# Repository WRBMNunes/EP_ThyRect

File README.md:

# EP_ThyRect
Educational plataform of closed-loop controlled thyristor rectifier designed to teach control systems

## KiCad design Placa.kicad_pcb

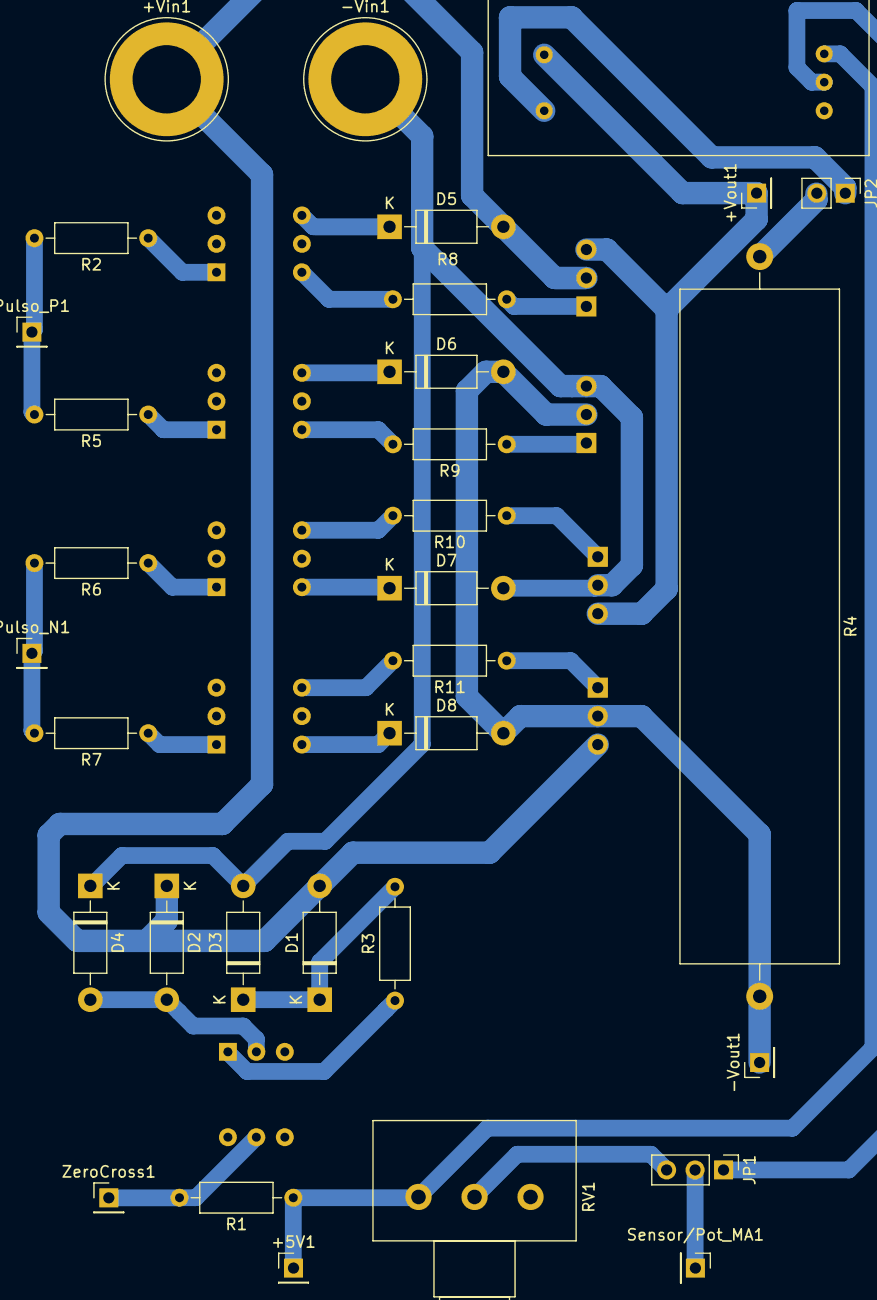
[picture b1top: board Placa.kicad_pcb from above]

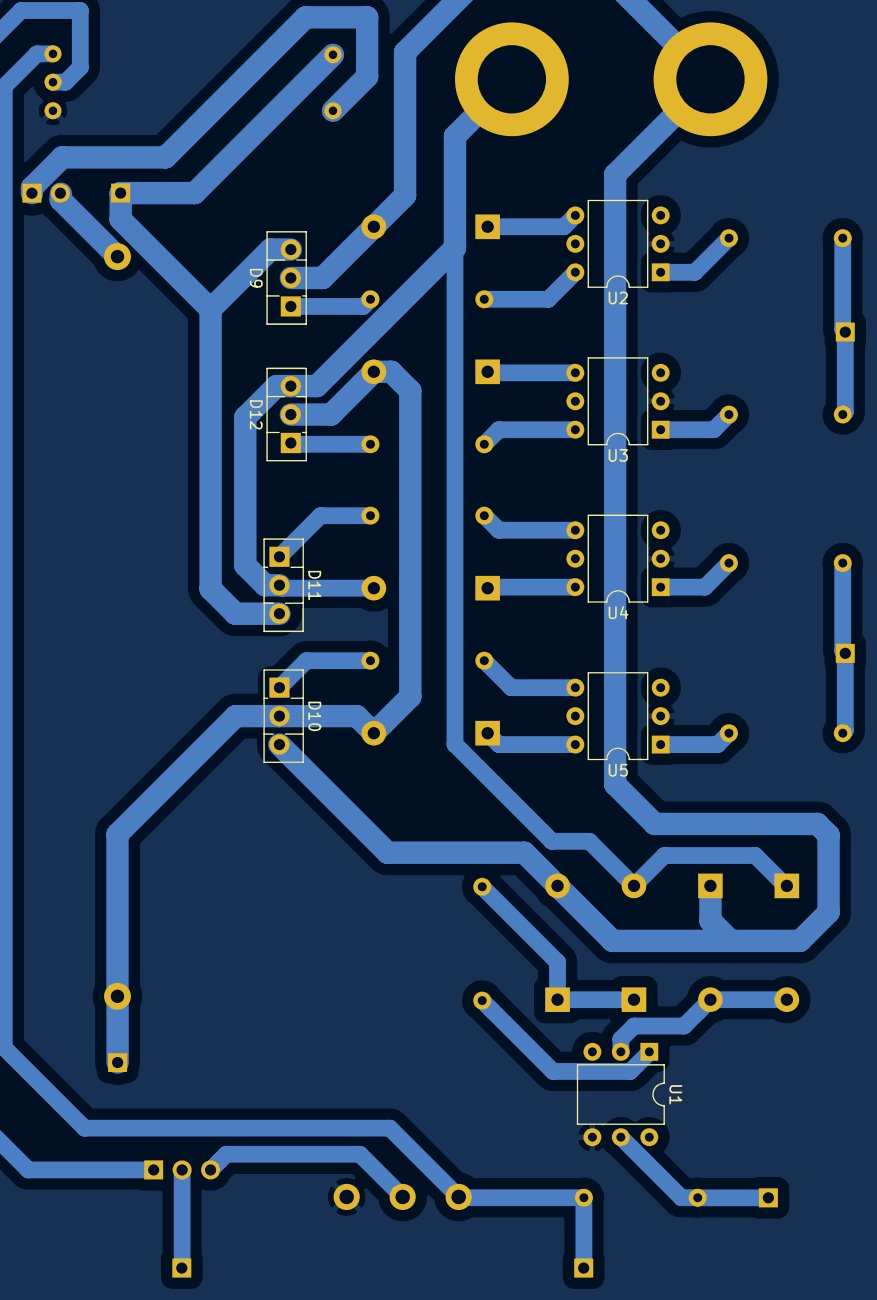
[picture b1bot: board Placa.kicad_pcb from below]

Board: 2 copper layers, 41 parts (9 on the bottom side), 33 nets.

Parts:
+5V1: Conn_01x01_Male; PinHeader_1x01_P2.54mm_Vertical
+Vin1: Conn_01x01_Female; Banana_Jack_1Pin
+Vout1: Conn_01x01_Female; PinHeader_1x01_P2.54mm_Vertical
-Vin1: Conn_01x01_Female; Banana_Jack_1Pin
-Vout1: Conn_01x01_Female; PinHeader_1x01_P2.54mm_Vertical
D1, D2, D3, D4, D5, D6, D7, D8: 1N4007; D_DO-41_SOD81_P10.16mm_Horizontal
D9, D10, D11, D12: Q_SCR_GAK; TO-126-3_Vertical
JP1: Jumper_3_Open; PinHeader_1x03_P2.54mm_Vertical
JP2: Jumper; PinHeader_1x02_P2.54mm_Vertical
Pulso_N1: Conn_01x01_Female; PinHeader_1x01_P2.54mm_Vertical
Pulso_P1: Conn_01x01_Female; PinHeader_1x01_P2.54mm_Vertical
R1: 10k; R_Axial_DIN0207_L6.3mm_D2.5mm_P10.16mm_Horizontal
R2, R5, R6, R7, R8, R9, R10, R11: 120; R_Axial_DIN0207_L6.3mm_D2.5mm_P10.16mm_Horizontal
R3: 470; R_Axial_DIN0207_L6.3mm_D2.5mm_P10.16mm_Horizontal
R4: 15; R_Axial_Power_L60.0mm_W14.0mm_P66.04mm
RV1: R_POT; Potentiometer_Alps_RK163_Single_Horizontal
Sensor/Pot_MA1: Conn_01x01_Female; PinHeader_1x01_P2.54mm_Vertical
U1: 4N25; DIP-6_W7.62mm
U2, U3, U4, U5: MOC3021M; DIP-6_W7.62mm
U6: ACS712xLCTR-05B; ACS712
ZeroCross1: Conn_01x01_Female; PinHeader_1x01_P2.54mm_Vertical

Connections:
5V: +5V1.1, R1.1, RV1.1, U6.8
A1: +Vin1.1, D1.2, D2.1, D5.2, D9.2, D10.3
A2: -Vout1.1, D6.2, D8.2, D10.2, D12.2, R4.2
A3: -Vin1.1, D3.2, D4.1, D7.2, D11.2, D12.3
ACS_Vout: JP1.1, U6.7
G1: D9.1, R8.1
G2: D12.1, R9.1
G3: D11.1, R10.1
G4: D10.1, R11.1
GND: RV1.3, U1.4, U2.2, U3.2, U4.2, U5.2, U6.5
unnamed: +Vout1.1, D9.3, D11.3, U6.1
unnamed: D1.1, D3.1, R3.2
unnamed: D2.2, D4.2, U1.2
unnamed: D5.1, U2.4
unnamed: D6.1, U3.4
unnamed: D7.1, U4.6
unnamed: D8.1, U5.6
unnamed: JP1.2, Sensor/Pot_MA1.1
unnamed: JP1.3, RV1.2
unnamed: JP2.1, U6.3
unnamed: JP2.2, R4.1
unnamed: Pulso_N1.1, R6.2, R7.2
unnamed: Pulso_P1.1, R2.2, R5.2
unnamed: R1.2, U1.5, ZeroCross1.1
unnamed: R2.1, U2.1
unnamed: R3.1, U1.1
unnamed: R5.1, U3.1
unnamed: R6.1, U4.1
unnamed: R7.1, U5.1
unnamed: R8.2, U2.6
unnamed: R9.2, U3.6
unnamed: R10.2, U4.4
unnamed: R11.2, U5.4

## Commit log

2023-08-02 Create Schematic
2023-08-02 Create OpenLoopCode
    Code for open loop operation
2023-08-02 Create ClosedLoopCode
    Code for closed-loop operation
